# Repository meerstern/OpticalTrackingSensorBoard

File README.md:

# Optical Tracking Sensor Board

## Feature
  * An optical tracking sensor board using PAT9125EL-TKIT manufactured by PixArt Imaging.  
  * It is possible to detect two-dimensional movement with one sensor.  
  * It can detect object movement at a distance of 1 to 30 mm.
  * No additional lens is required.  
  * Programmable resolution up to 1,275cpi.  
  * It can be easily connected via I2C (Grove compatible connector).  
  * This board is equipped with voltage level conversion, so it can be directly connected to 5V systems such as Arduino Uno.  

## Application
  * Tracking on a Moving Surface  
  * Tracking on the Side of a Rotational Shaft
  
## Note
  * Power/I2C 3.3V-5V  
  * This board is equipped with the PAT9125EL-TKIT, which is an I2C connection type, and does not support SPI connection.

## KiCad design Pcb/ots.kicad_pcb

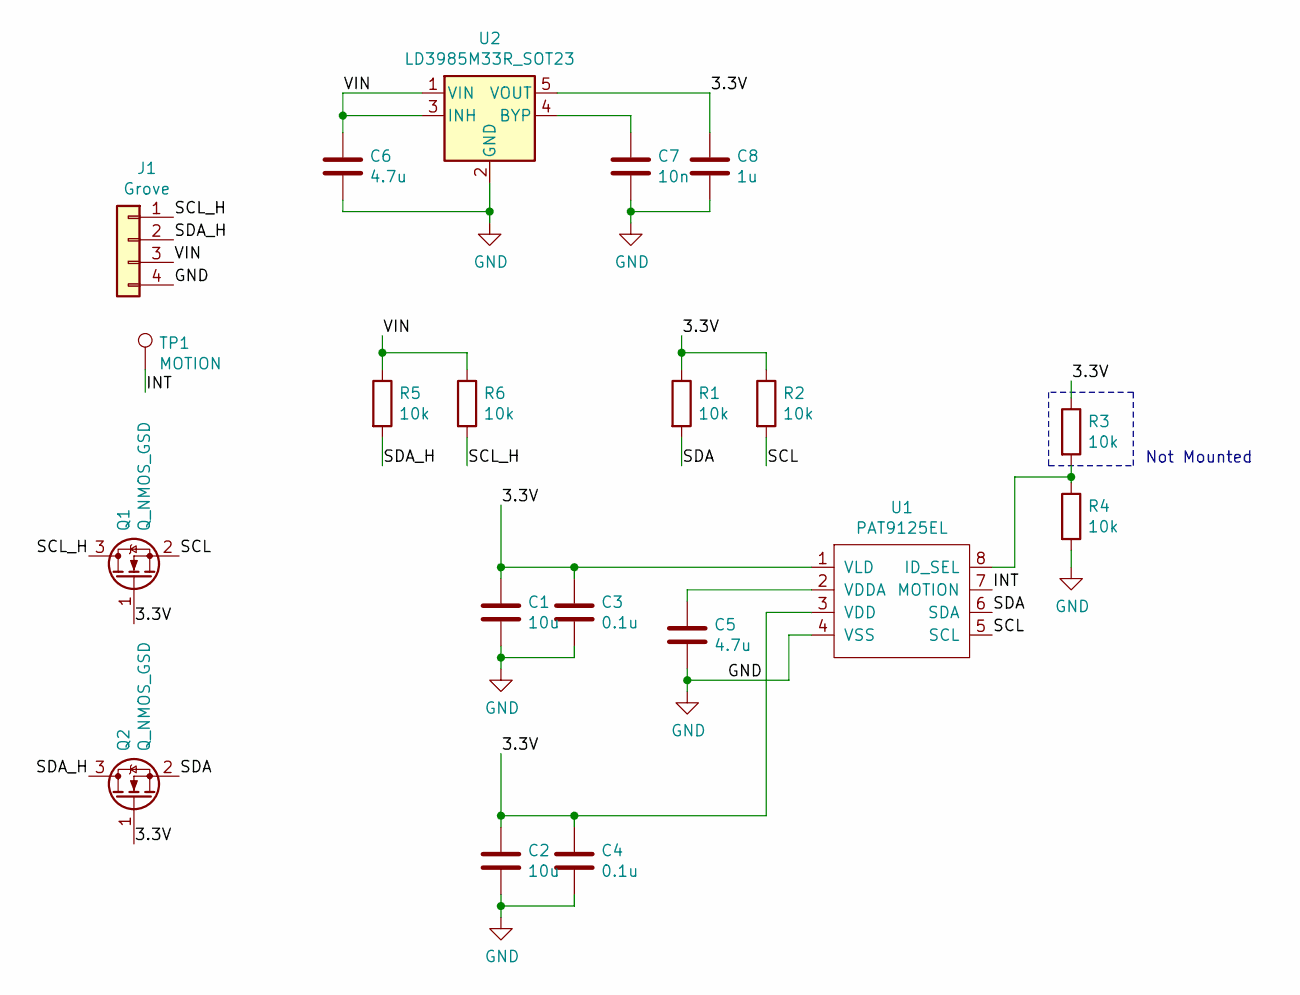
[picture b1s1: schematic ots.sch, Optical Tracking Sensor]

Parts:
C1, C2: 10u; C_0805_2012Metric
C3, C4: 0.1u; C_0603_1608Metric
C5, C6: 4.7u; C_0805_2012Metric
C7: 10n; C_0603_1608Metric
C8: 1u; C_0603_1608Metric
J1: Grove; GROVE
Q1, Q2: Q_NMOS_GSD; SOT-23
R1, R2, R3, R4, R5, R6: 10k; R_0603_1608Metric
TP1: MOTION; TestPoint_THTPad_D1.0mm_Drill0.5mm
U1: PAT9125EL
U2: LD3985M33R_SOT23; SOT-23-5

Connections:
/3.3V: C1.1, C2.1, C3.1, C4.1, C8.1, Q1.1 (G), Q2.1 (G), R1.1, R2.1, R3.1, U1.1 (VLD), U1.3 (VDD), U2.5 (VOUT)
/INT: TP1.1, U1.7 (MOTION)
/SCL: Q1.2 (S), R2.2, U1.5 (SCL)
/SCL_H: J1.1, Q1.3 (D), R6.2
/SDA: Q2.2 (S), R1.2, U1.6 (SDA)
/SDA_H: J1.2, Q2.3 (D), R5.2
/VIN: C6.1, J1.3, R5.1, R6.1, U2.1 (VIN), U2.3 (INH)
GND: C1.2, C2.2, C3.2, C4.2, C5.2, C6.2, C7.2, C8.2, J1.4, R4.2, U1.4 (VSS), U2.2 (GND)
unnamed: C5.1, U1.2 (VDDA)
unnamed: C7.1, U2.4 (BYP)
unnamed: R3.2, R4.1, U1.8 (ID_SEL)

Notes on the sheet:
Not Mounted

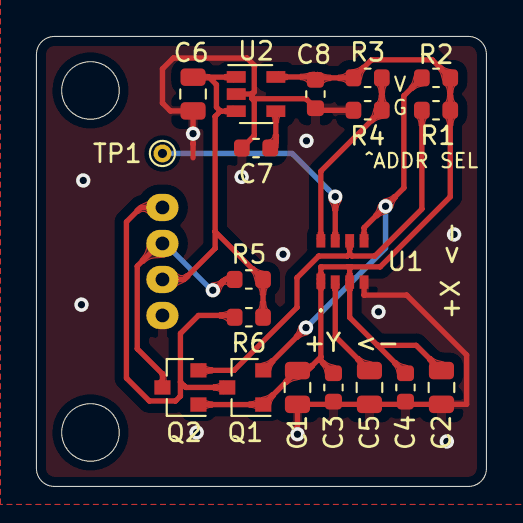
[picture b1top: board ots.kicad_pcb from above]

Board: 2 copper layers, 25.0 x 25.0 mm, 22 parts (1 on the bottom side), 11 nets.

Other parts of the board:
REF1, REF2: MountingHole_3.2mm_M3

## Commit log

2025-09-28 Add Files
2025-11-07 Add images
